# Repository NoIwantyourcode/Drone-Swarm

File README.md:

# Drone Swarm

This is a group of 2 drones which are autonoumously controlled by a ground controller to fly in specific patterns, the drone swarm will have 2 drones (this is expandable) and a ground controller, They ground controller will supply instructions to the drone on how to fly and where to fly, The drones will you use their Accelerometers, Gyroscopes and magnetometers to carry out these instructions and fly in a pattern.

# How does it work?

The drones are individually controlled by an onboard flight controller, Each flight controller is connected to the ESP32-S3 ground station which supplies commands to the drones for them to perform it. The ground station recieves input data on the drones location, height and distance from each other from 2 phones, one under and one below which track the the drones. this allows the ground station to have accurate locations for the drones and direct them individually!

The ground station is currently a bare ESP32-S3 DevBoard which is connected to my computer, It features nothing special but it does connect to both drones in a shared connection to supply commands to them. The commands have id's so so the both drones will not follow the same command. There is no case to increase connection strength as the connection won't be blocked by the plastic

# How is it powered

The ground station is connected to my computer and that how it recieves power, The dones have an onboard Lithium-Ion battery at 3.7v to power them for roughly 4 -5 minutes of flght time!

# Why I made this?

I made this as it links to my passion in aviation and I think it is a great way to get started with autonomous flight!

# Connection diagram!

1. Dotted lines represent Non-physical connections (Bluetooth, wifi, ESP-NOW)
2. Solid lines represent physical connections (cables)

# Schematics

# PCB

# PCB rendered

# Drone frame

# Assembled view

# Fully assembled picture

# Demo link!

Heres the link to a demo video: [https://youtube.com/shorts/X6EJljXOPJc?feature=share](https://youtube.com/shorts/X6EJljXOPJc?feature=share)

# Note for reviewer
The PCB in my assembled view doesn't contain any 3D files for the components as freeCAD would not let me export the components it gathered from my raw PCB file.
The board is also 4 layers and has components on both sides

Lapse also wasn't working for a big part of the design so I wasn't really a record a ton. I only got the first ~1h20mins

Using JLCPCB to 3D print my drone frame as it is in ABS, If I can't use JLC3DP I'll try to find someone through printing legion

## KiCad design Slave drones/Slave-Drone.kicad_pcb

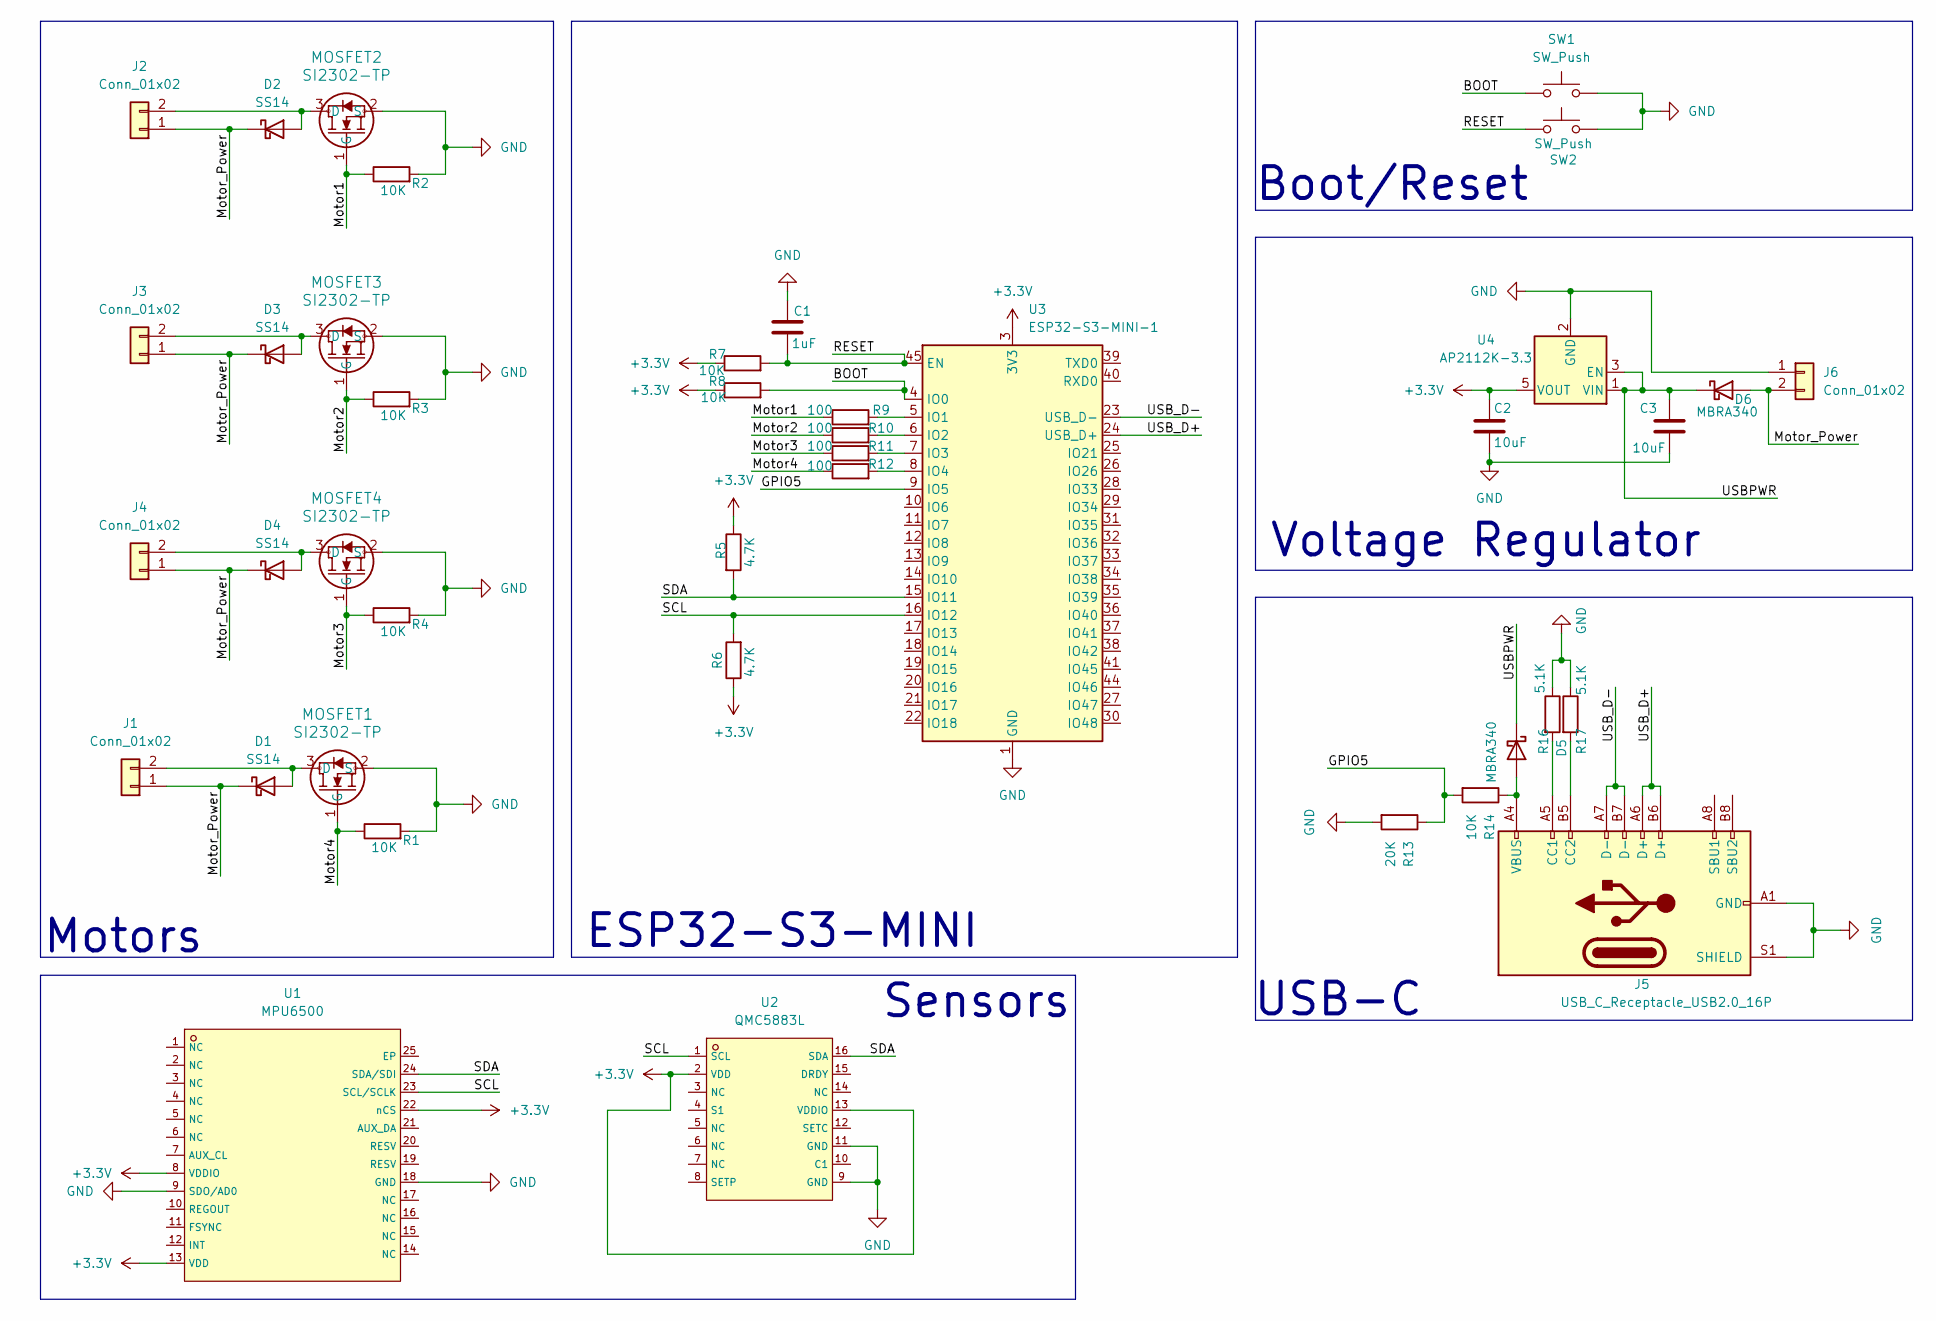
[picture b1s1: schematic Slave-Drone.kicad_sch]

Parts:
C1: 1uF; C_0402_1005Metric
C2, C3: 10uF; C_0603_1608Metric
D1, D2, D3, D4: SS14; D_SMA
D5, D6: MBRA340; D_SMA
J1, J2, J3, J4, J6: Conn_01x02; PinHeader_1x02_P2.54mm_Vertical
J5: USB_C_Receptacle_USB2.0_16P; USB_C_Receptacle_HCTL_HC-TYPE-C-16P-01A
MOSFET1, MOSFET2, MOSFET3, MOSFET4: SI2302-TP; SOT-23_MCC
R1, R2, R3, R4, R7, R8: 10K; R_0402_1005Metric
R5, R6: 4.7K; R_0402_1005Metric
R9, R10, R11, R12: 100; R_0402_1005Metric
R13: 20K; R_0402_1005Metric_Pad0.72x0.64mm_HandSolder
R14: 10K; R_0402_1005Metric_Pad0.72x0.64mm_HandSolder
R16, R17: 5.1K; R_0402_1005Metric
SW1, SW2: SW_Push; SW_Push_SPST_NO_Alps_SKRK
U1: MPU6500; InvenSense_QFN-24_3x3mm_P0.4mm; LCSC C50278
U2: QMC5883L; QMC5883L_QST; LCSC C976032
U3: ESP32-S3-MINI-1; XCVR_ESP32-S3-MINI-1-N8
U4: AP2112K-3.3; SOT-23-5

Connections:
+3.3V: C2.1, R5.1, R6.1, R7.1, R8.1, U1.8 (VDDIO), U1.13 (VDD), U1.22 (nCS), U2.2 (VDD), U2.13 (VDDIO), U3.3 (3V3), U4.5 (VOUT)
/BOOT: R8.2, SW1.1, U3.4 (IO0)
/GPIO5: R13.1, R14.2, U3.9 (IO5)
/Motor1: MOSFET2.1 (G), R2.1, R9.1
/Motor2: MOSFET3.1 (G), R3.1, R10.1
/Motor3: MOSFET4.1 (G), R4.1, R11.1
/Motor4: MOSFET1.1 (G), R1.1, R12.1
/Motor_Power: D1.1 (K), D2.1 (K), D3.1 (K), D4.1 (K), D6.2 (A), J1.1, J2.1, J3.1, J4.1, J6.2
/RESET: C1.2, R7.2, SW2.1, U3.45 (EN)
/SCL: R6.2, U1.23 (SCL/SCLK), U2.1 (SCL), U3.16 (IO12)
/SDA: R5.2, U1.24 (SDA/SDI), U2.16 (SDA), U3.15 (IO11)
/USBPWR: C3.1, D5.1 (K), D6.1 (K), U4.1 (VIN), U4.3 (EN)
/USB_D+: J5.A6 (D+), J5.B6 (D+), U3.24 (USB_D+)
/USB_D-: J5.A7 (D-), J5.B7 (D-), U3.23 (USB_D-)
GND: C1.1, C2.2, C3.2, J5.A1 (GND), J5.A12 (GND), J5.B1 (GND), J5.B12 (GND), J5.S1 (SHIELD), J6.1, MOSFET1.2 (S), MOSFET2.2 (S), MOSFET3.2 (S), MOSFET4.2 (S), R1.2, R2.2, R3.2, R4.2, R13.2, R16.1, R17.1, SW1.2, SW2.2, U1.9 (SDO/AD0), U1.18 (GND), U2.9 (GND), U2.11 (GND), U3.1 (GND), U3.2 (GND), U3.42 (GND), U3.43 (GND), U3.46 (GND), U3.47 (GND), U3.48 (GND), U3.49 (GND), U3.50 (GND), U3.51 (GND), U3.52 (GND), U3.53 (GND), U3.54 (GND), U3.55 (GND), U3.56 (GND), U3.57 (GND), U3.58 (GND), U3.59 (GND), U3.60 (GND), U3.61 (GND), U3.62 (GND), U3.63 (GND), U3.64 (GND), U3.65 (GND), U4.2 (GND)
unnamed: D1.2 (A), J1.2, MOSFET1.3 (D)
unnamed: D2.2 (A), J2.2, MOSFET2.3 (D)
unnamed: D3.2 (A), J3.2, MOSFET3.3 (D)
unnamed: D4.2 (A), J4.2, MOSFET4.3 (D)
unnamed: D5.2 (A), J5.A4 (VBUS), J5.A9 (VBUS), J5.B4 (VBUS), J5.B9 (VBUS), R14.1
unnamed: J5.A5 (CC1), R16.2
unnamed: J5.B5 (CC2), R17.2
unnamed: R9.2, U3.5 (IO1)
unnamed: R10.2, U3.6 (IO2)
unnamed: R11.2, U3.7 (IO3)
unnamed: R12.2, U3.8 (IO4)

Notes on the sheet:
USB-C
ESP32-S3-MINI
Voltage Regulator
Sensors
Motors
Boot/Reset

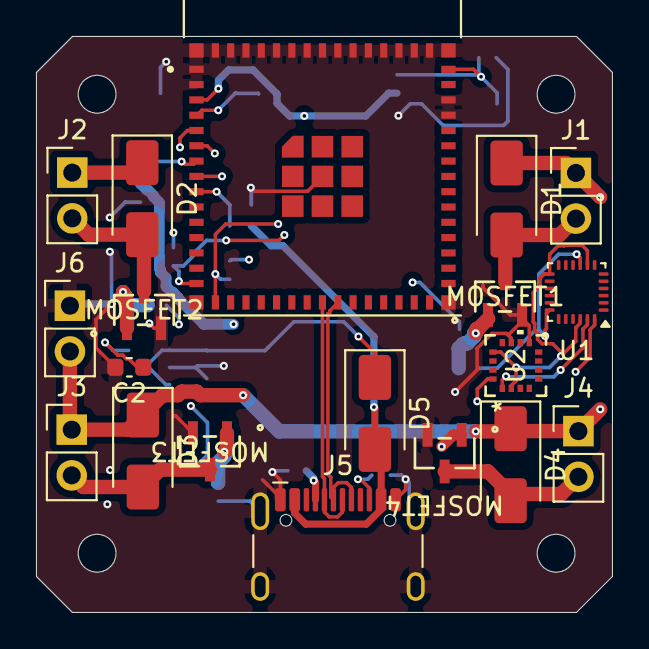
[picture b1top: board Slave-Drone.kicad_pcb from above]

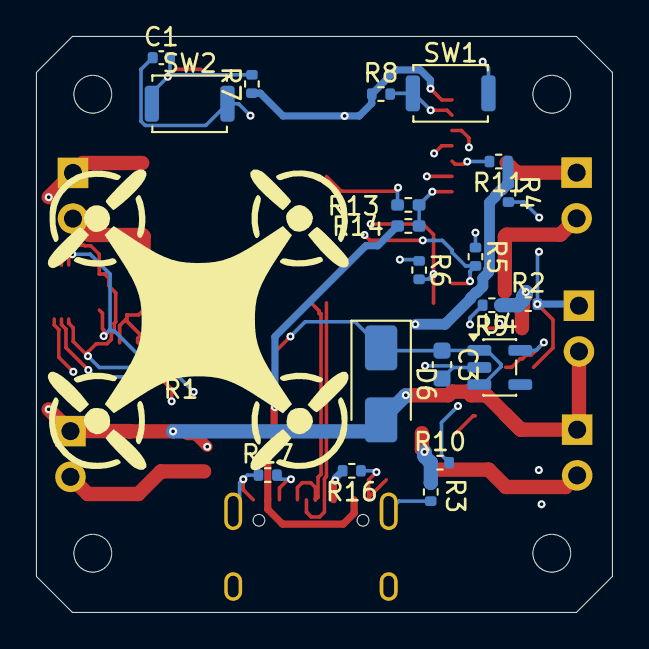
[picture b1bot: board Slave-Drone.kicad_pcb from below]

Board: 4 copper layers, 32.0 x 32.0 mm, 45 parts (26 on the bottom side), 26 nets.

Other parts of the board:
M1, M2, M3, M4: MountingHole_2.1mm

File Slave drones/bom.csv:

Slave Drone,,Total Price: 181.70,,,
,,,,,
,,,,,
,,,,,
Component,Value,Product link,Qty,Total Price ($),Notes
Capacitor,1uF,https://jlcpcb.com/partdetail/53938-CL05A105KA5NQNC/C52923,20,0.106,
Capacitor,10uF,https://jlcpcb.com/partdetail/20411-CL10A106KP8NNNC/C19702,40,0.592,
Diode,SS14,https://jlcpcb.com/partdetail/MDD_Microdiode_Semiconductor-S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,18,0.3024,
Diode,MBRA340,https://jlcpcb.com/partdetail/FUXINSEMI-MBRA340T3GFS/C5563736,10,0.796,
USB-C,USB_C_Receptacle_USB2.0_16P,https://jlcpcb.com/partdetail/HCTL-HC_TYPE_C_16P01A/C2894897,2,0.1972,
MOSFET,SI2302-TP,https://jlcpcb.com/partdetail/79111-SI2302TP/C77977,12,0.5268,
Resistor,10K,https://jlcpcb.com/partdetail/26487-0402WGF1002TCE/C25744,24,0.0312,
Resistor,4.7K,https://jlcpcb.com/partdetail/26643-0402WGF4701TCE/C25900,20,0.02,
Resistor,100,https://jlcpcb.com/partdetail/25819-0402WGF1000TCE/C25076,20,0.02,
Resistor,20K,https://jlcpcb.com/partdetail/26508-0402WGF2002TCE/C25765,20,0.02,
Resistor,5.1K,https://jlcpcb.com/partdetail/26648-0402WGF5101TCE/C25905,20,0.018,
IMU,MPU6500,https://jlcpcb.com/partdetail/TDKInvenSense-MPU6500/C50278,2,9.0042,
ESP32-S3,ESP32-S3-MINI-1,https://jlcpcb.com/partdetail/EspressifSystems-ESP32_S3_MINI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,2,9.3612,
Voltage Regulator,AP2112K-3.3,https://jlcpcb.com/partdetail/TECHPUBLIC-AP2112K_33TRG1/C23380830,5,0.542,
Magnetometer,QMC5883P,https://jlcpcb.com/partdetail/QST-QMC5883P/C2847467,2,3.05,Changed to P instead of L due to part shortages || Board changed || Same footprint
1x02 pin header,Conn_01x02,https://www.lcsc.com/product-detail/C42431804.html?s_z=n_q_l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,1,0.45,Self assembled || Comes in 20 pins
SMD Push button,SW_Push,https://jlcpcb.com/partdetail/ALPSALPINE-SKRKAHE020/C202388,2,0.87,
CW Motor,,https://www.aliexpress.com/item/1005006132824490.html?spm=a2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,4,8.13,
CCW Motor,,https://www.aliexpress.com/item/1005006132824490.html?spm=a2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,4,8.24,
Propellers,,,,,
,,,Total Parts price,42.277,
,,,Total Price (PCBA fees incl),165.58,
,,,Total pric with shipping,169.13,
Ground Station,,,,,
,,,,,
,,,,,
,,,,,
Component,Value,Product link,Qty,Total Price ($),Notes
ESP32-S3,,,,12.56,Communicates to all the drones simoultaneously
3D print case,,,,0,
,,,,,
,,,,,
,,,Total Price of all components:,181.69,

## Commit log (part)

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2026-06-07 Completed Schematics for Drone Slave
2026-06-07 Completely routed the PCB
2026-06-07 added silkscreen art
2026-06-07 silkscreen art
2026-06-07 shifted sensors to the front
2026-06-08 changed QMC5338L to QMC5338P
    Has the same symbol/footprint but slightly different wiring
2026-06-08 Added bom
2026-06-09 tried to fix PCB
2026-06-09 I broke the pcb file, had to restart routing
2026-06-09 tried fixing error 3 - failed - use work around
2026-06-09 corrected mosfet placement
2026-06-09 nothing
2026-06-09 Added firmware
2026-06-09 updated bom.csv
2026-06-09 something
2026-06-09 Updated BOM and added case files
2026-06-10 added external tracking
2026-06-10 fixes
2026-06-10 added standoffs for drone case and updated BOM
2026-06-10 updated images
2026-06-10 added PID control, allows the drone to fly
2026-06-10 update images for drone case
    Updated images for drone frame and assembled view in README.
2026-06-10 added additional support arms
2026-06-11 removed any vias that were on pads
2026-06-11 removed all vias on pads
2026-06-12 Updated via hole size
2026-06-13 updated QMC5883P/MPU6500/ESP32 footprints
